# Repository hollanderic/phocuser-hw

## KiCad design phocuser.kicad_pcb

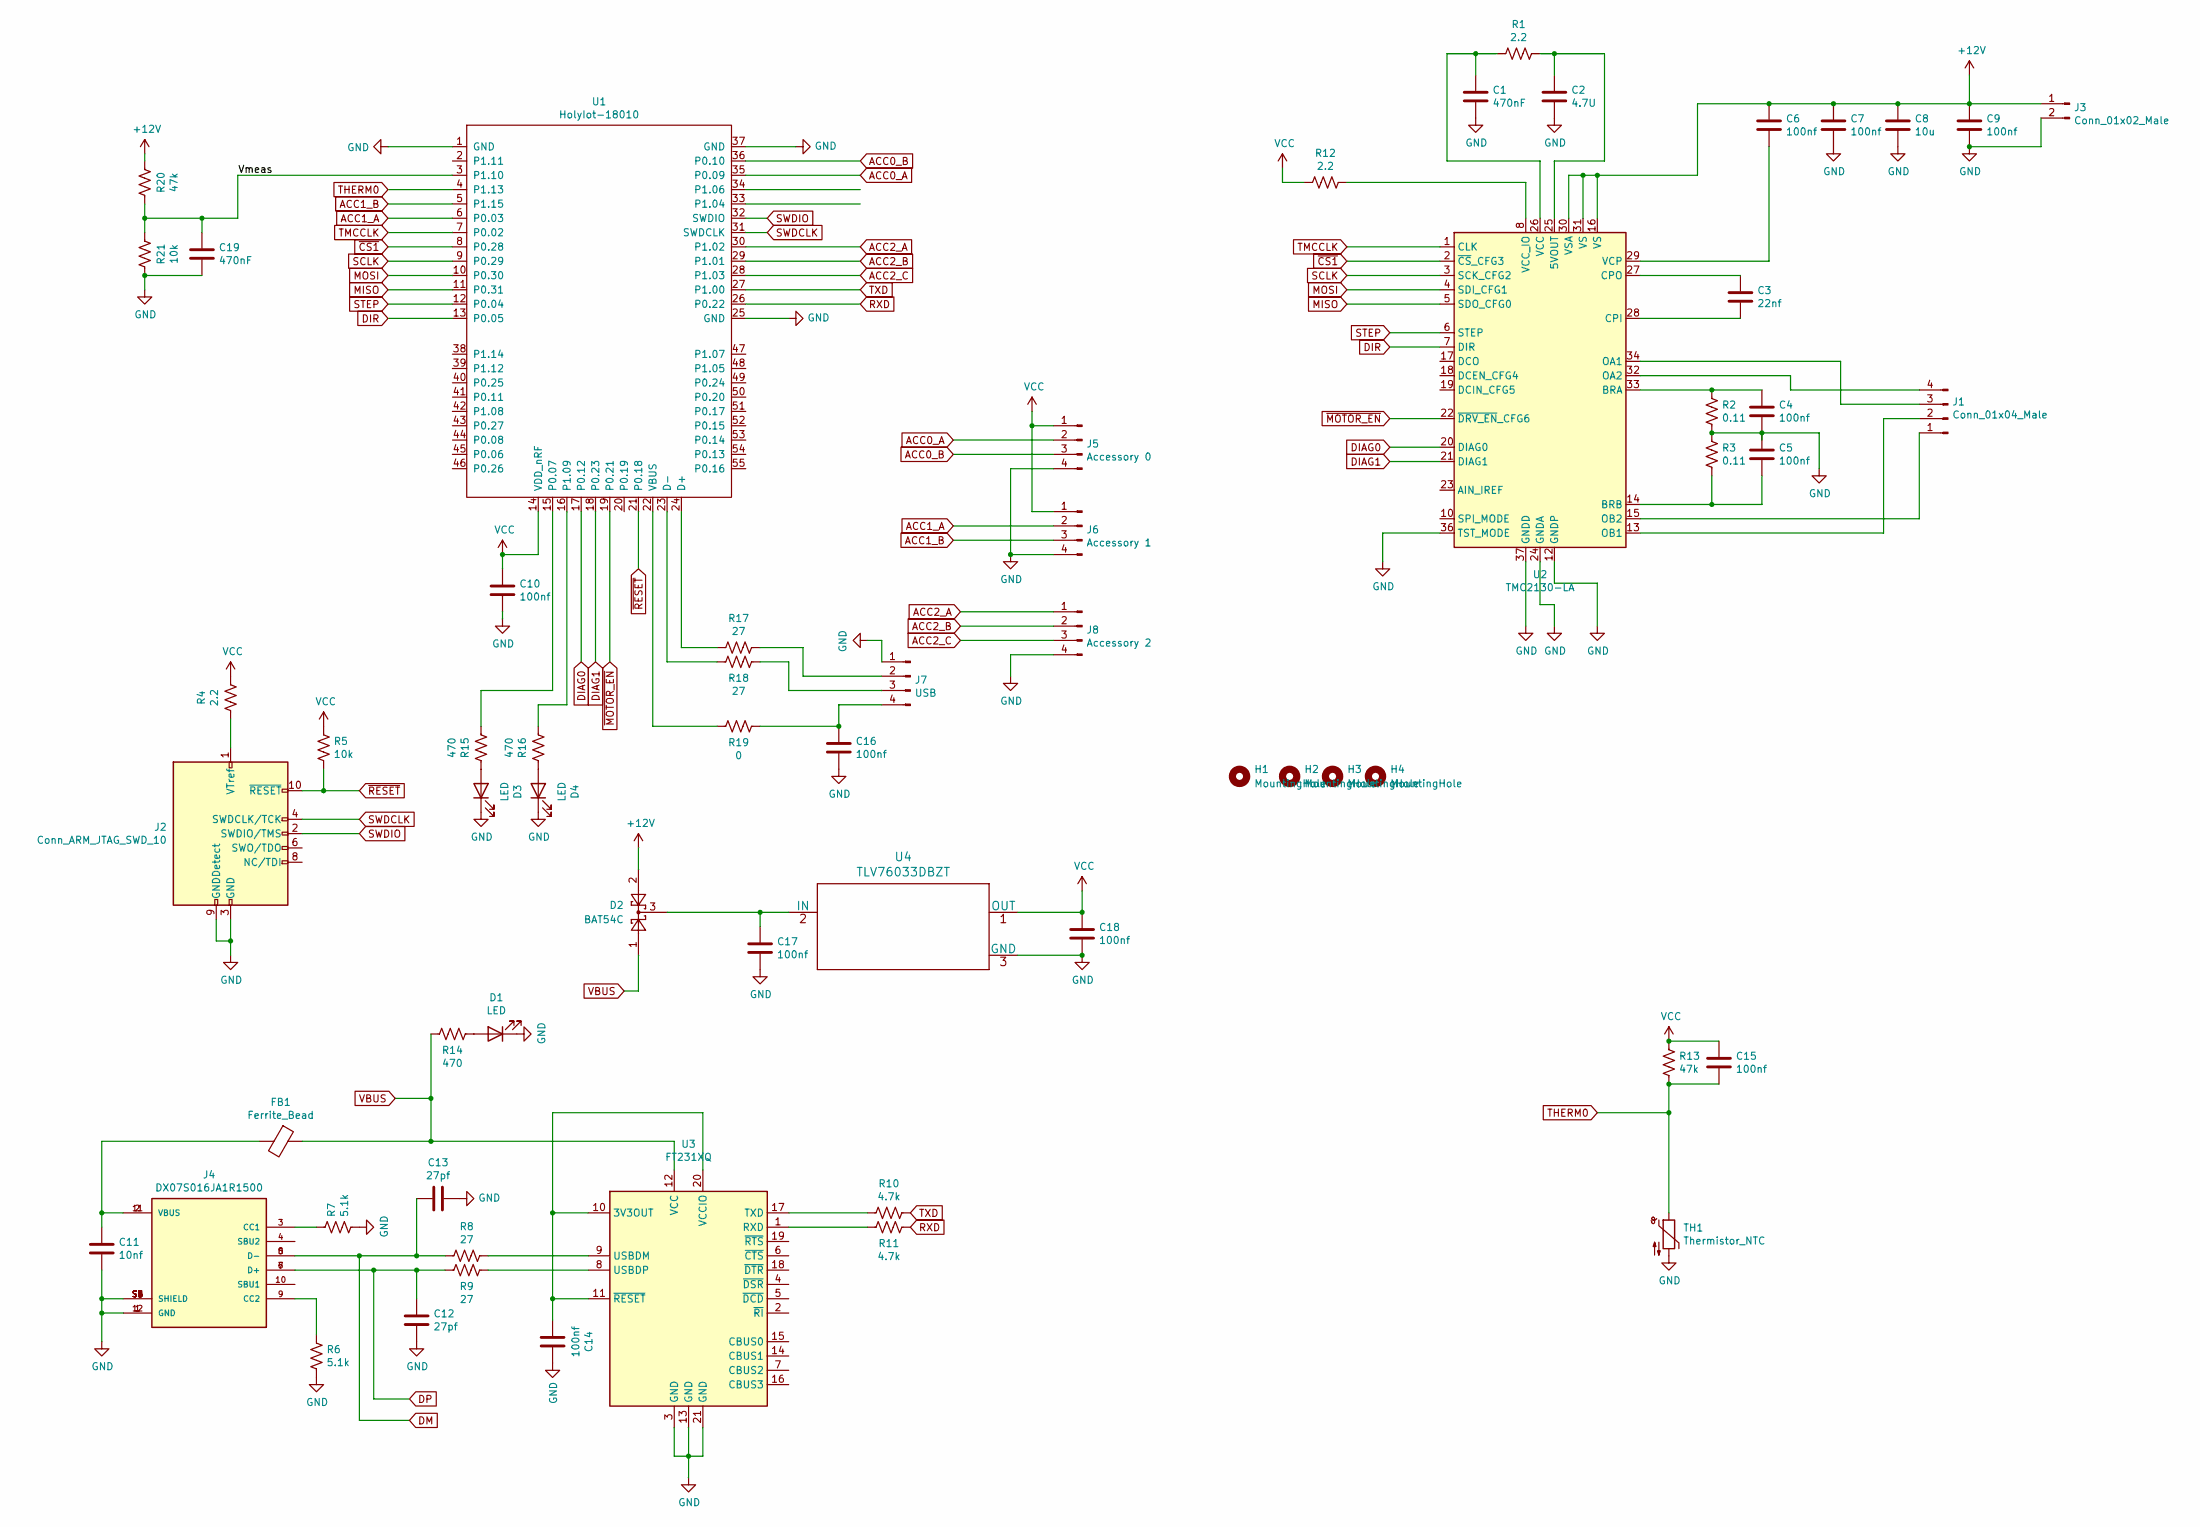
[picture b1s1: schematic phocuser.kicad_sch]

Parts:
C1, C19: 470nF; C_0402_1005Metric
C2: 4.7U; C_0805_2012Metric
C3: 22nf; C_0402_1005Metric
C4, C5, C6, C7, C9, C10, C14, C15, C16, C17, C18: 100nf; C_0402_1005Metric
C8: 10u; C_0805_2012Metric
C11: 10nf; C_0402_1005Metric
C12, C13: 27pf; C_0402_1005Metric
D1, D3, D4: LED; LED_0603_1608Metric
D2: BAT54C; SOT-23
FB1: Ferrite_Bead; L_0402_1005Metric
H1, H2, H3, H4: MountingHole; MountingHole_2.2mm_M2
J1: Conn_01x04_Male; JST_XH_B4B-XH-A_1x04_P2.50mm_Vertical
J2: Conn_ARM_JTAG_SWD_10; PinHeader_2x05_P1.27mm_Vertical_SMD
J3: Conn_01x02_Male; JST_XH_B2B-XH-AM_1x02_P2.50mm_Vertical
J4: DX07S016JA1R1500; JAE_DX07S016JA1R1500; PARTREV 1
J5: Accessory 0; JST_PH_B4B-PH-K_1x04_P2.00mm_Vertical
J6: Accessory 1; JST_PH_B4B-PH-K_1x04_P2.00mm_Vertical
J7: USB; JST_PH_B4B-PH-K_1x04_P2.00mm_Vertical
J8: Accessory 2; JST_PH_B4B-PH-K_1x04_P2.00mm_Vertical
R1, R4, R12: 2.2; R_0402_1005Metric
R2, R3: 0.11; R_0805_2012Metric
R5, R21: 10k; R_0402_1005Metric
R6, R7: 5.1k; R_0402_1005Metric
R8, R9, R17, R18: 27; R_0402_1005Metric
R10, R11: 4.7k; R_0402_1005Metric
R13, R20: 47k; R_0402_1005Metric
R14, R15, R16: 470; R_0402_1005Metric
R19: 0; R_0402_1005Metric
TH1: Thermistor_NTC; R_0402_1005Metric
U1: HolyIot-18010; HOLYIOT-18010
U2: TMC2130-LA; QFN-36-1EP_5x6mm_P0.5mm_EP3.6x4.1mm_ThermalVias
U3: FT231XQ; QFN-20-1EP_4x4mm_P0.5mm_EP2.5x2.5mm_ThermalVias
U4: TLV76033DBZT

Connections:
+12V: C6.1, C7.1, C8.1, C9.1, D2.2, J3.1, R20.1, U2.16 (VS), U2.30 (VSA), U2.31 (VS)
/Vmeas: C19.1, R20.2, R21.1, U1.3 (P1.10)
ACC0_A: J5.2, U1.35 (P0.09)
ACC0_B: J5.3, U1.36 (P0.10)
ACC1_A: J6.2, U1.6 (P0.03)
ACC1_B: J6.3, U1.5 (P1.15)
ACC2_A: J8.1, U1.30 (P1.02)
ACC2_B: J8.2, U1.29 (P1.01)
ACC2_C: J8.3, U1.28 (P1.03)
DIAG0: U1.17 (P0.12), U2.20 (DIAG0)
DIAG1: U1.18 (P0.23), U2.21 (DIAG1)
DIR: U1.13 (P0.05), U2.7 (DIR)
DM: C13.2, J4.5 (D-), J4.8 (D-), R8.2
DP: C12.1, J4.6 (D+), J4.7 (D+), R9.2
GND: C1.2, C2.2, C4.2, C5.1, C7.2, C8.2, C9.2, C10.2, C11.2, C12.2, C13.1, C14.1, C16.2, C17.2, C18.2, C19.2, D1.1 (K), D3.1 (K), D4.1 (K), J2.3 (GND), J2.5 (GND), J2.9 (GNDDetect), J3.2, J4.1 (GND), J4.12 (GND), J4.S1 (SHIELD), J4.S2 (SHIELD), J4.S3 (SHIELD), J4.S4 (SHIELD), J4.S5 (SHIELD), J4.S6 (SHIELD), J5.4, J6.4, J7.1, J8.4, R2.1, R3.2, R6.2, R7.2, R21.2, TH1.2, U1.1 (GND), U1.25 (GND), U1.37 (GND), U2.11 (GNDD), U2.12 (GNDP), U2.24 (GNDA), U2.35 (GNDP), U2.36 (TST_MODE), U2.37 (GNDD), U3.3 (GND), U3.13 (GND), U3.21 (GND), U4.3 (GND)
MISO: U1.11 (P0.31), U2.5 (SDO_CFG0)
MOSI: U1.10 (P0.30), U2.4 (SDI_CFG1)
unnamed: C1.1, R1.2, U2.26 (VCC)
unnamed: C2.1, R1.1, U2.25 (5VOUT)
unnamed: C3.1, U2.27 (CPO)
unnamed: C3.2, U2.28 (CPI)
unnamed: C4.1, R2.2, U2.33 (BRA)
unnamed: C5.2, R3.1, U2.14 (BRB)
unnamed: C6.2, U2.29 (VCP)
unnamed: C11.1, FB1.2, J4.2 (VBUS), J4.11 (VBUS)
unnamed: C14.2, U3.10 (3V3OUT), U3.11 (~RESET), U3.20 (VCCIO)
unnamed: C16.1, J7.4, R19.1
unnamed: C17.1, D2.3, U4.2 (IN)
unnamed: D1.2 (A), R14.1
unnamed: D3.2 (A), R15.1
unnamed: D4.2 (A), R16.1
unnamed: J1.1, U2.15 (OB2)
unnamed: J1.2, U2.13 (OB1)
unnamed: J1.3, U2.34 (OA1)
unnamed: J1.4, U2.32 (OA2)
unnamed: J2.1 (VTref), R4.2
unnamed: J4.3 (CC1), R7.1
unnamed: J4.9 (CC2), R6.1
unnamed: J7.2, R17.1
unnamed: J7.3, R18.1
unnamed: R8.1, U3.9 (USBDM)
unnamed: R9.1, U3.8 (USBDP)
unnamed: R10.2, U3.17 (TXD)
unnamed: R11.2, U3.1 (RXD)
unnamed: R12.1, U2.8 (VCC_IO)
unnamed: R17.2, U1.24 (D+)
unnamed: R18.2, U1.23 (D-)
unnamed: R19.2, U1.22 (VBUS)
unnamed: R15.2, U1.15 (P0.07)
unnamed: R16.2, U1.16 (P1.09)
RXD: R11.1, U1.26 (P0.22)
SCLK: U1.9 (P0.29), U2.3 (SCK_CFG2)
STEP: U1.12 (P0.04), U2.6 (STEP)
SWDCLK: J2.4 (SWDCLK/TCK), U1.31 (SWDCLK)
SWDIO: J2.2 (SWDIO/TMS), U1.32 (SWDIO)
THERM0: C15.2, R13.1, TH1.1, U1.4 (P1.13)
TMCCLK: U1.7 (P0.02), U2.1 (CLK)
TXD: R10.1, U1.27 (P1.00)
VBUS: D2.1, FB1.1, R14.2, U3.12 (VCC)
VCC: C10.1, C15.1, C18.1, J5.1, J6.1, R4.1, R5.1, R12.2, R13.2, U1.14 (VDD_nRF), U4.1 (OUT)
~CS1: U1.8 (P0.28), U2.2 (~CS_CFG3)
~MOTOR_EN: U1.19 (P0.21), U2.22 (~DRV_EN_CFG6)
~RESET: J2.10 (~RESET), R5.2, U1.21 (P0.18)

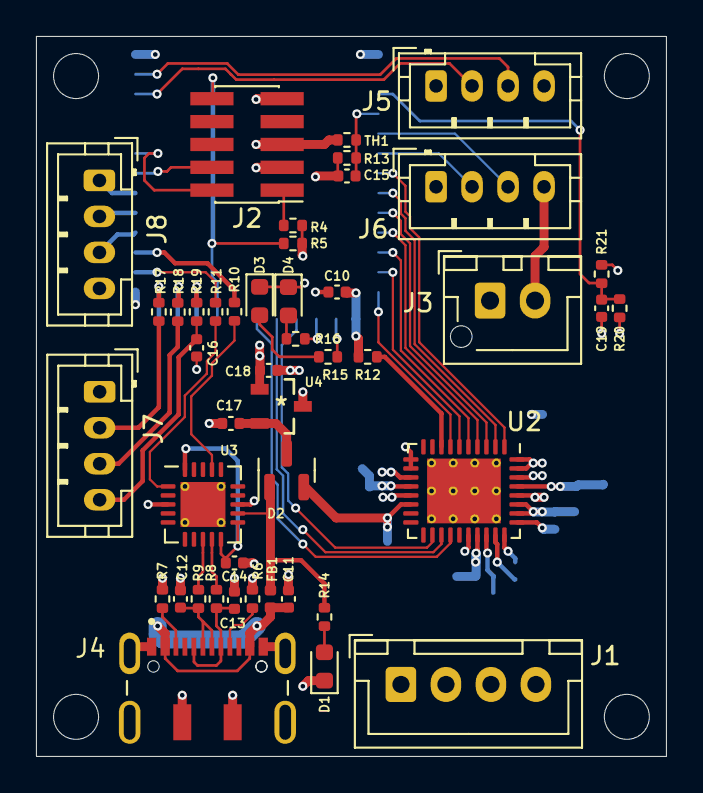
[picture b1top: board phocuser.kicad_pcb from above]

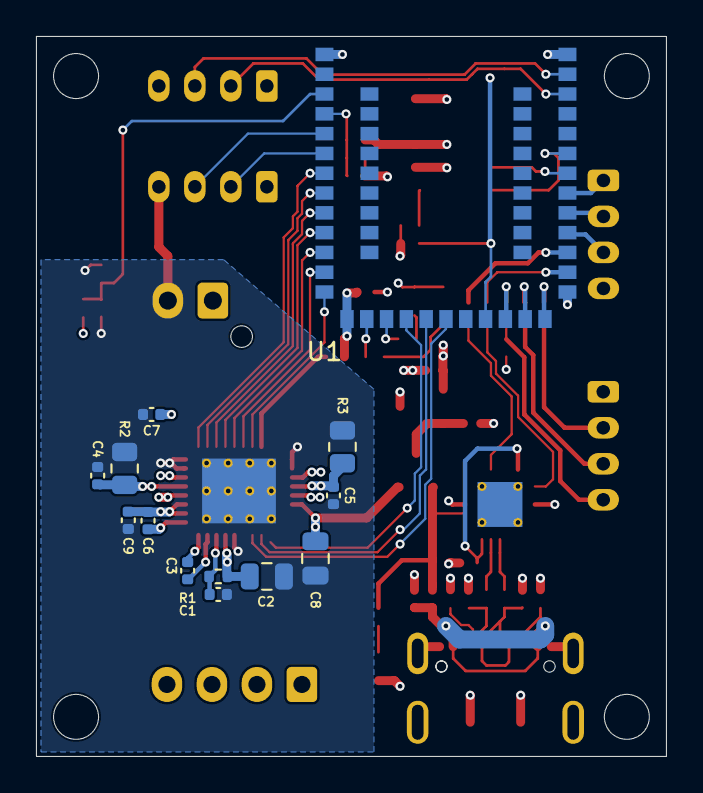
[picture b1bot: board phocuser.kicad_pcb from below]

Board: 4 copper layers, 35.0 x 40.0 mm, 62 parts (13 on the bottom side), 63 nets.

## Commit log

2021-02-22 checkin
2021-02-23 Layout incremental checkin
2021-02-28 layout complete
2022-09-11 cleanup and move to kicad 6.0
2022-09-12 edits
2022-09-15 Design sent to OshPark 9/14/2022
2022-09-15 fixed untracked files

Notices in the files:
parts and their libraries:
Copyright 2016 Accelerated Designs. All rights reserved.
